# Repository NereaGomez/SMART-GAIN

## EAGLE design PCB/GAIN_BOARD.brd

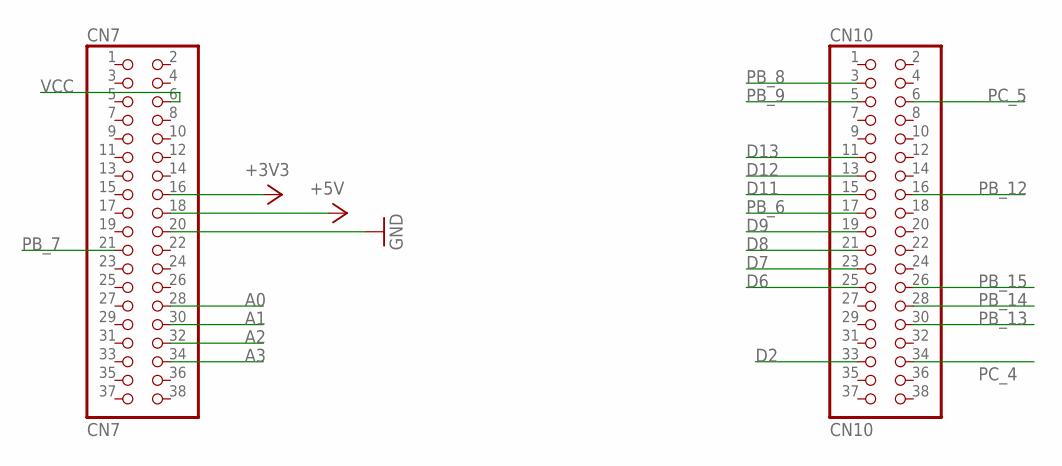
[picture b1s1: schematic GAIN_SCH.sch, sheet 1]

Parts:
CN7: CN7; 2X19
CN10: CN10; 2X19

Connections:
+3V3: CN7.16; also elsewhere on the board
+5V: CN7.18; also elsewhere on the board
A0: CN7.28; also elsewhere on the board
A1: CN7.30; also elsewhere on the board
A2: CN7.32; also elsewhere on the board
A3: CN7.34; also elsewhere on the board
D2: CN10.33; also elsewhere on the board
D6: CN10.25; also elsewhere on the board
D7: CN10.23; also elsewhere on the board
D8: CN10.21; also elsewhere on the board
D9: CN10.19; also elsewhere on the board
D11: CN10.15; also elsewhere on the board
D12: CN10.13; also elsewhere on the board
D13: CN10.11; also elsewhere on the board
GND: CN7.20; also elsewhere on the board
PB_6: CN10.17; also elsewhere on the board
PB_7: CN7.21; also elsewhere on the board
PB_8: CN10.3; also elsewhere on the board
PB_9: CN10.5; also elsewhere on the board
PB_12: CN10.16; also elsewhere on the board
PB_13: CN10.30; also elsewhere on the board
PB_14: CN10.28; also elsewhere on the board
PB_15: CN10.26; also elsewhere on the board
PC_4: CN10.34; also elsewhere on the board
PC_5: CN10.6; also elsewhere on the board
VCC: CN7.6; also elsewhere on the board

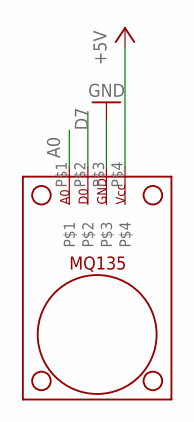
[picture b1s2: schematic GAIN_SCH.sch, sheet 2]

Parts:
U$1: MQ135

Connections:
+5V: U$1.P$4; also elsewhere on the board
A0: U$1.P$1; also elsewhere on the board
D7: U$1.P$2; also elsewhere on the board
GND: U$1.P$3; also elsewhere on the board

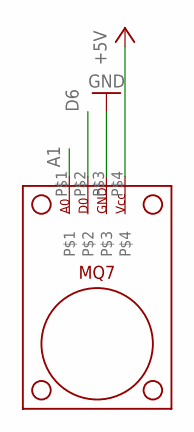
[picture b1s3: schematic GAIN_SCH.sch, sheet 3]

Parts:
U$2: MQ7

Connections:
+5V: U$2.P$4; also elsewhere on the board
A1: U$2.P$1; also elsewhere on the board
D6: U$2.P$2; also elsewhere on the board
GND: U$2.P$3; also elsewhere on the board

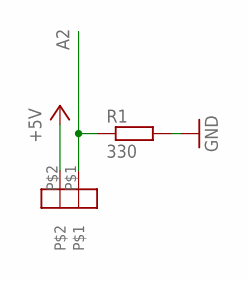
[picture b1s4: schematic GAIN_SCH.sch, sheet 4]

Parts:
R1: 330; 0207/10
U$3: LDR

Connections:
+5V: U$3.P$2; also elsewhere on the board
A2: R1.1, U$3.P$1; also elsewhere on the board
GND: R1.2; also elsewhere on the board

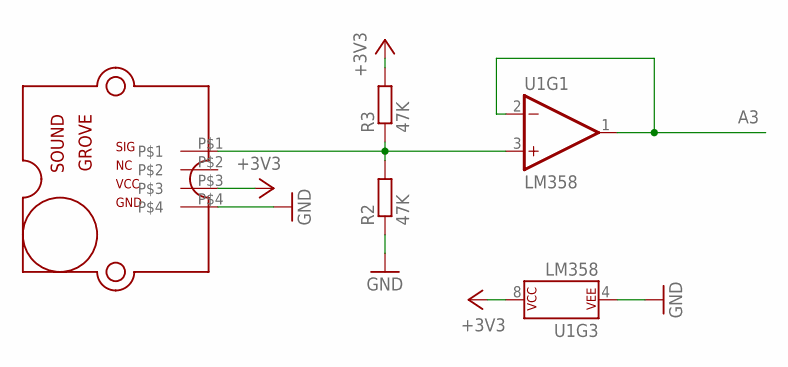
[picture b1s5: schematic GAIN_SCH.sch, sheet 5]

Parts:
R2, R3: 47K; 0207/10
U1: LM358; DIP08
U$4: GROVE_SOUND

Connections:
+3V3: R3.2, U1.8 (P$V+), U$4.P$3; also elsewhere on the board
A3: U1.1 (OUT), U1.2 (-IN); also elsewhere on the board
GND: R2.1, U1.4 (P$V-), U$4.P$4; also elsewhere on the board
unnamed: R2.2, R3.1, U1.3 (+IN), U$4.P$1

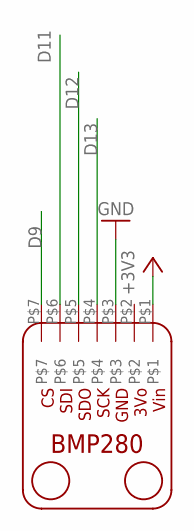
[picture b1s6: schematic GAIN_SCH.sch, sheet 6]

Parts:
U$5: BMP280

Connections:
+3V3: U$5.P$1; also elsewhere on the board
D9: U$5.P$7; also elsewhere on the board
D11: U$5.P$6; also elsewhere on the board
D12: U$5.P$5; also elsewhere on the board
D13: U$5.P$4; also elsewhere on the board
GND: U$5.P$3; also elsewhere on the board

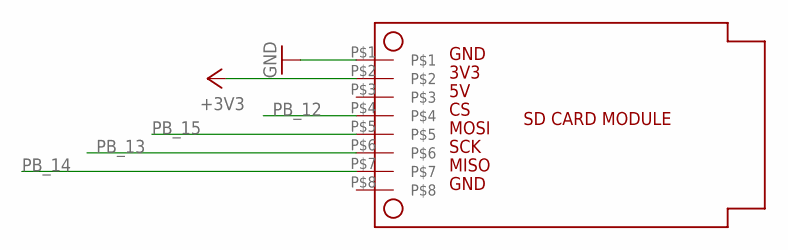
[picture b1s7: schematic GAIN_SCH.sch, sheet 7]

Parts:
U$6: SD_CARD

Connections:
+3V3: U$6.P$2; also elsewhere on the board
GND: U$6.P$1; also elsewhere on the board
PB_12: U$6.P$4; also elsewhere on the board
PB_13: U$6.P$6; also elsewhere on the board
PB_14: U$6.P$7; also elsewhere on the board
PB_15: U$6.P$5; also elsewhere on the board

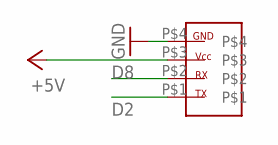
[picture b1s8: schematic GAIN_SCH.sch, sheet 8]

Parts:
U$10: CO2_GROVE

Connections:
+5V: U$10.P$3; also elsewhere on the board
D2: U$10.P$1; also elsewhere on the board
D8: U$10.P$2; also elsewhere on the board
GND: U$10.P$4; also elsewhere on the board

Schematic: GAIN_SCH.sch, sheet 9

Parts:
CAN_VCC: CAN_VCC; 1X01
U$7: CAN_BREADBOARD; CAN_BREAKBOARD

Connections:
+5V: CAN_VCC.1, U$7.P$1; also elsewhere on the board
GND: U$7.P$4; also elsewhere on the board
PB_8: U$7.P$3; also elsewhere on the board
PB_9: U$7.P$2; also elsewhere on the board

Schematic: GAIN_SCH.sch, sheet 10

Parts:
R4, R5: 10K; 0207/10
U$8: SI7021

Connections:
+3V3: R4.2, R5.2, U$8.P$3; also elsewhere on the board
GND: U$8.P$4; also elsewhere on the board
PB_6: R4.1, U$8.P$1; also elsewhere on the board
PB_7: R5.1, U$8.P$2; also elsewhere on the board

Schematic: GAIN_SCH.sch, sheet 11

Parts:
U$9: FONA

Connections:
+3V3: U$9.P$4; also elsewhere on the board
+5V: U$9.P$1; also elsewhere on the board
GND: U$9.P$3, U$9.P$9; also elsewhere on the board
PC_4: U$9.P$6; also elsewhere on the board
PC_5: U$9.P$7; also elsewhere on the board

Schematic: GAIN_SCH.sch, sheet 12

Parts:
C1: 0.33 uF; C050-030X075
C2: 0.1 uF; C050-030X075
IC1: 7805T; TO220H
X1: W237-102

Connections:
GND: C1.1, C2.1, IC1.2 (GND), X1.2; also elsewhere on the board
unnamed: C1.2, IC1.1 (VI), X1.1
VCC: C2.2, IC1.3 (VO); also elsewhere on the board

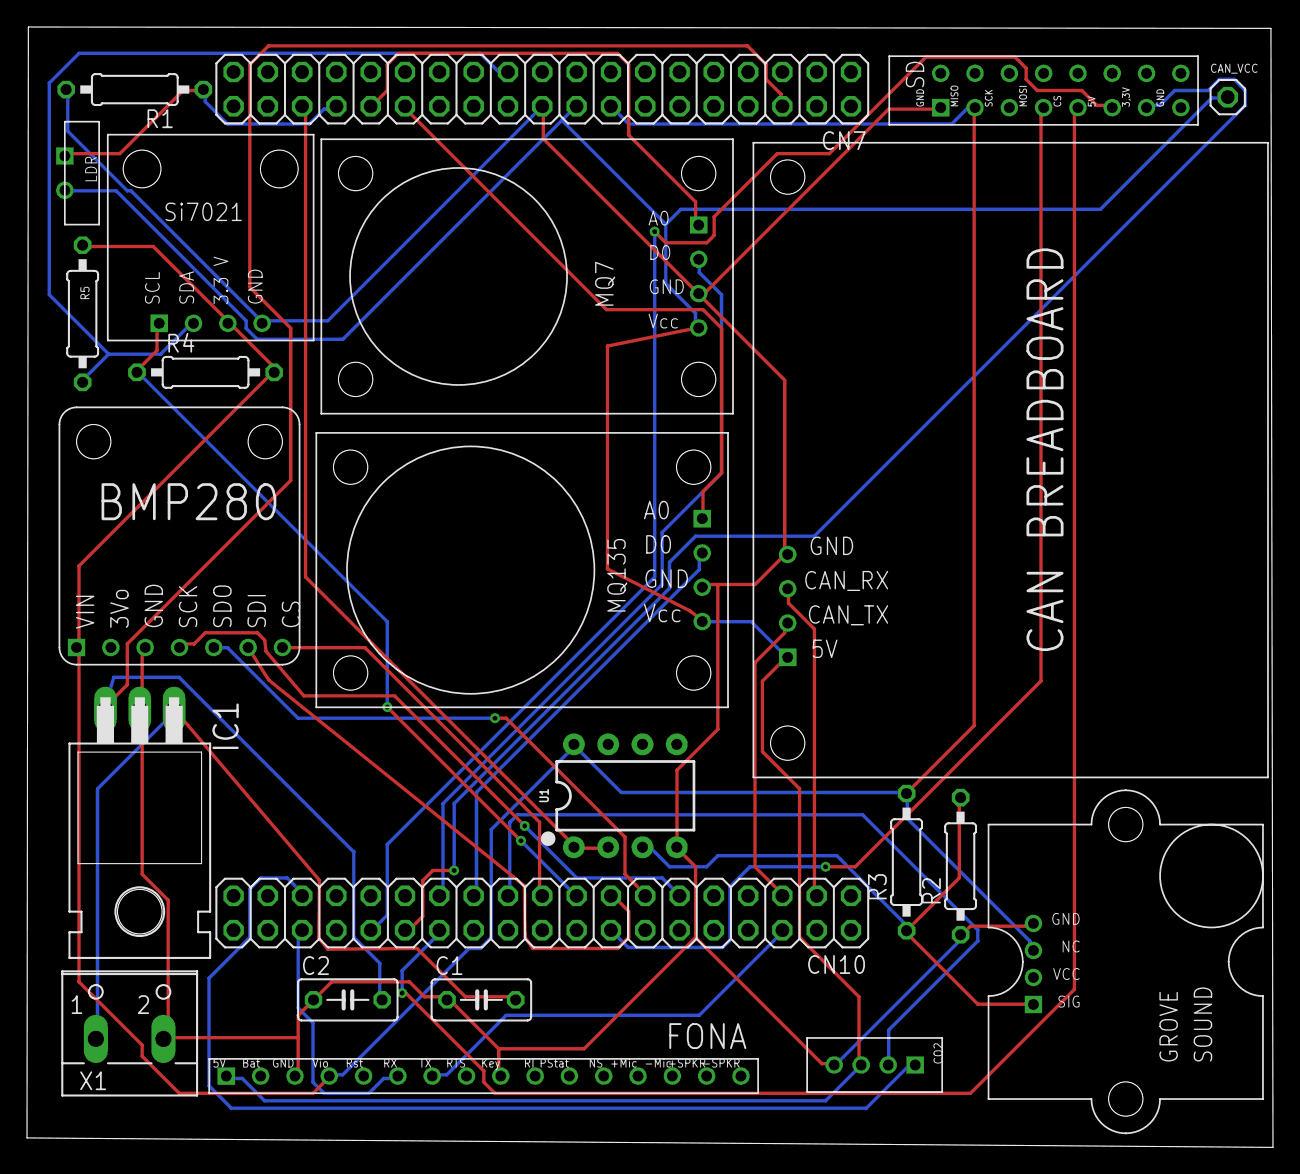
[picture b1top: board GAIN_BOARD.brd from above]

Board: 2 copper layers, 92.2 x 83.0 mm, 23 parts (0 on the bottom side), 28 nets.

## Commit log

2017-08-26 primer commit

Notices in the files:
parts and their libraries:
SparkFun-IC-Amplifiers: Licensing: Creative Commons ShareAlike 4.0 International - https://creativecommons.org/licenses/by-sa/4.0
